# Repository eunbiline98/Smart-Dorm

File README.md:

# Smart-Dorm

## This is my mini project, which i implemented in my dorm, to make my dorm look high tech 😆😆😆

# Hardware
- Esp-8266 (nodemcu  / wemos)
- Relay Module 2 CH
- DHT 11
- Magnetic Sensor
- Door Lock 12V
- PSU 5V 3A and 12V 1A

# Schematic

# PCB Layout

# Software
- Arduino IDE
- Thinger.Io Platform

# Fiture
- Control on/off relay lamp
- Control lock/unlock Door Lock
- Monitoring Temperature & Humidity
- Monitoring Door Status

# Documentation
- Module Smart Dorm By Atmduino Product

link Buy : https://www.tokopedia.com/atmduinorobotic/smart-home-2-channel-relay

- Thinger.io Dashboard

# Update

- Support Google firebase Realtime Database 
- Mit App's Inventor
- https://www.electronicwings.com/users/eunbiline98/projects/770/making-a-remote-lamp-using-nodemcu-esp-8266-iot

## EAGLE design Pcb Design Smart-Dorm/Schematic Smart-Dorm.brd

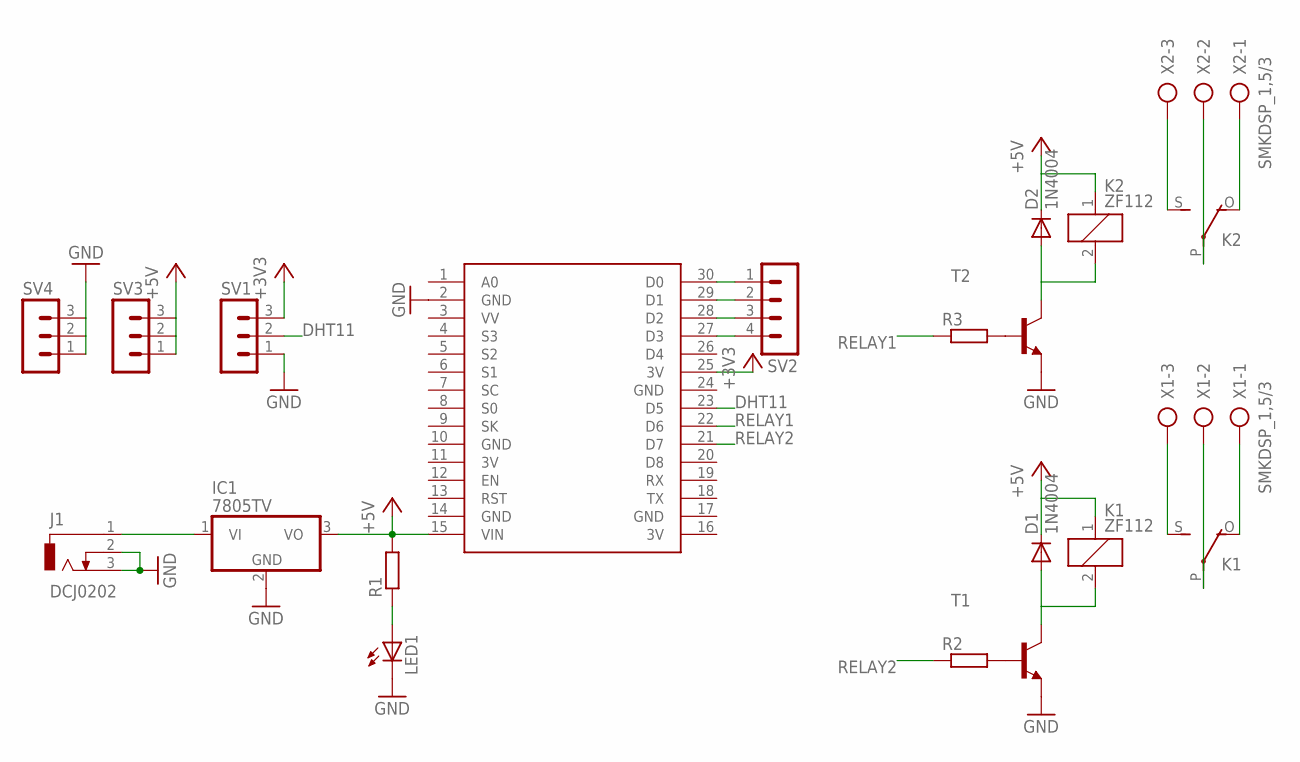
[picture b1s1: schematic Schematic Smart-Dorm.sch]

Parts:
D1, D2: 1N4004; DO41-10
IC1: 7805TV; TO220V
J1: DCJ0202
K1, K2: ZF112
LED1: LED5MM
R1, R2, R3: R-EU_0207/10; 0207/10
SV1, SV3, SV4: MA03-1
SV2: MA04-1
T1, T2: 2N2222-NPN-TO18-EBC; TO18
U$1: NODEMCU
X1, X2: SMKDSP_1,5/3

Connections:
3V: U$1.11 (3V), U$1.16 (3V)
+3V3: SV1.3, U$1.25 (3V)
+5V: D1.C, D2.C, IC1.3 (VO), K1.1, K2.1, R1.2, SV3.1, SV3.2, SV3.3, U$1.15 (VIN)
DHT11: SV1.2, U$1.23 (D5)
GND: IC1.2 (GND), J1.2, J1.3, LED1.K (C), SV1.1, SV4.1, SV4.2, SV4.3, T1.1 (E), T2.1 (E), U$1.2 (GND), U$1.10 (GND), U$1.14 (GND), U$1.17 (GND), U$1.24 (GND)
unnamed: K1.S, X1.3
unnamed: LED1.A, R1.1
unnamed: IC1.1 (VI), J1.1
unnamed: D1.A, K1.2, T1.3 (C)
unnamed: K1.O, X1.1
unnamed: SV2.1, U$1.30 (D0)
unnamed: SV2.2, U$1.29 (D1)
unnamed: SV2.3, U$1.28 (D2)
unnamed: SV2.4, U$1.27 (D3)
unnamed: K1.P, X1.2
unnamed: R2.2, T1.2 (B)
unnamed: D2.A, K2.2, T2.3 (C)
unnamed: R3.2, T2.2 (B)
unnamed: K2.S, X2.3
unnamed: K2.O, X2.1
unnamed: K2.P, X2.2
RELAY1: R3.1, U$1.22 (D6)
RELAY2: R2.1, U$1.21 (D7)

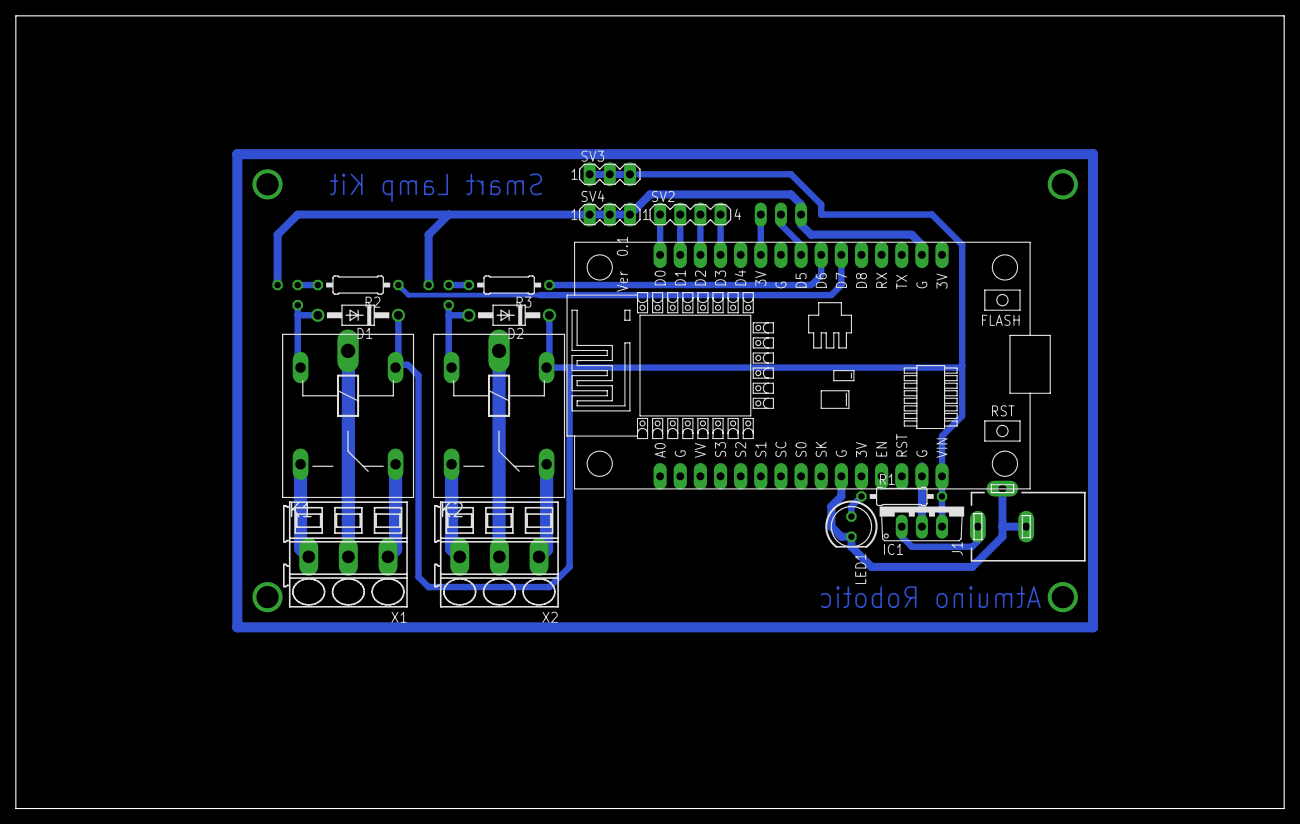
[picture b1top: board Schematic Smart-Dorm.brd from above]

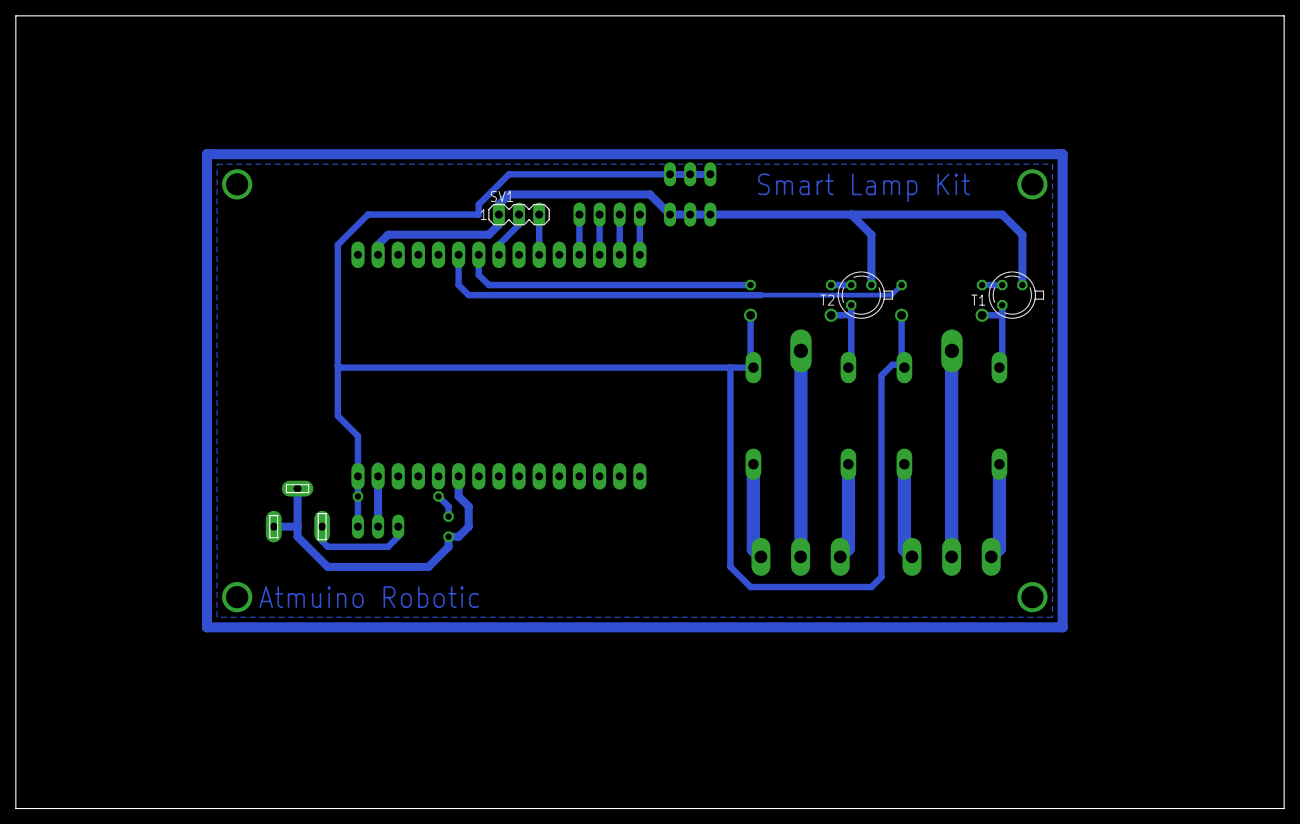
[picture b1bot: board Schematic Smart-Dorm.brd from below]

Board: 2 copper layers, 160.0 x 100.0 mm, 19 parts (3 on the bottom side), 23 nets.

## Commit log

2021-07-15 Upload Thinger.io Connection
2021-07-23 Adding Pcb Design
